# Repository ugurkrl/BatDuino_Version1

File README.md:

BatDuino V1
MAX17040 / MAX17043 + TP4056A + ATMEGA328P

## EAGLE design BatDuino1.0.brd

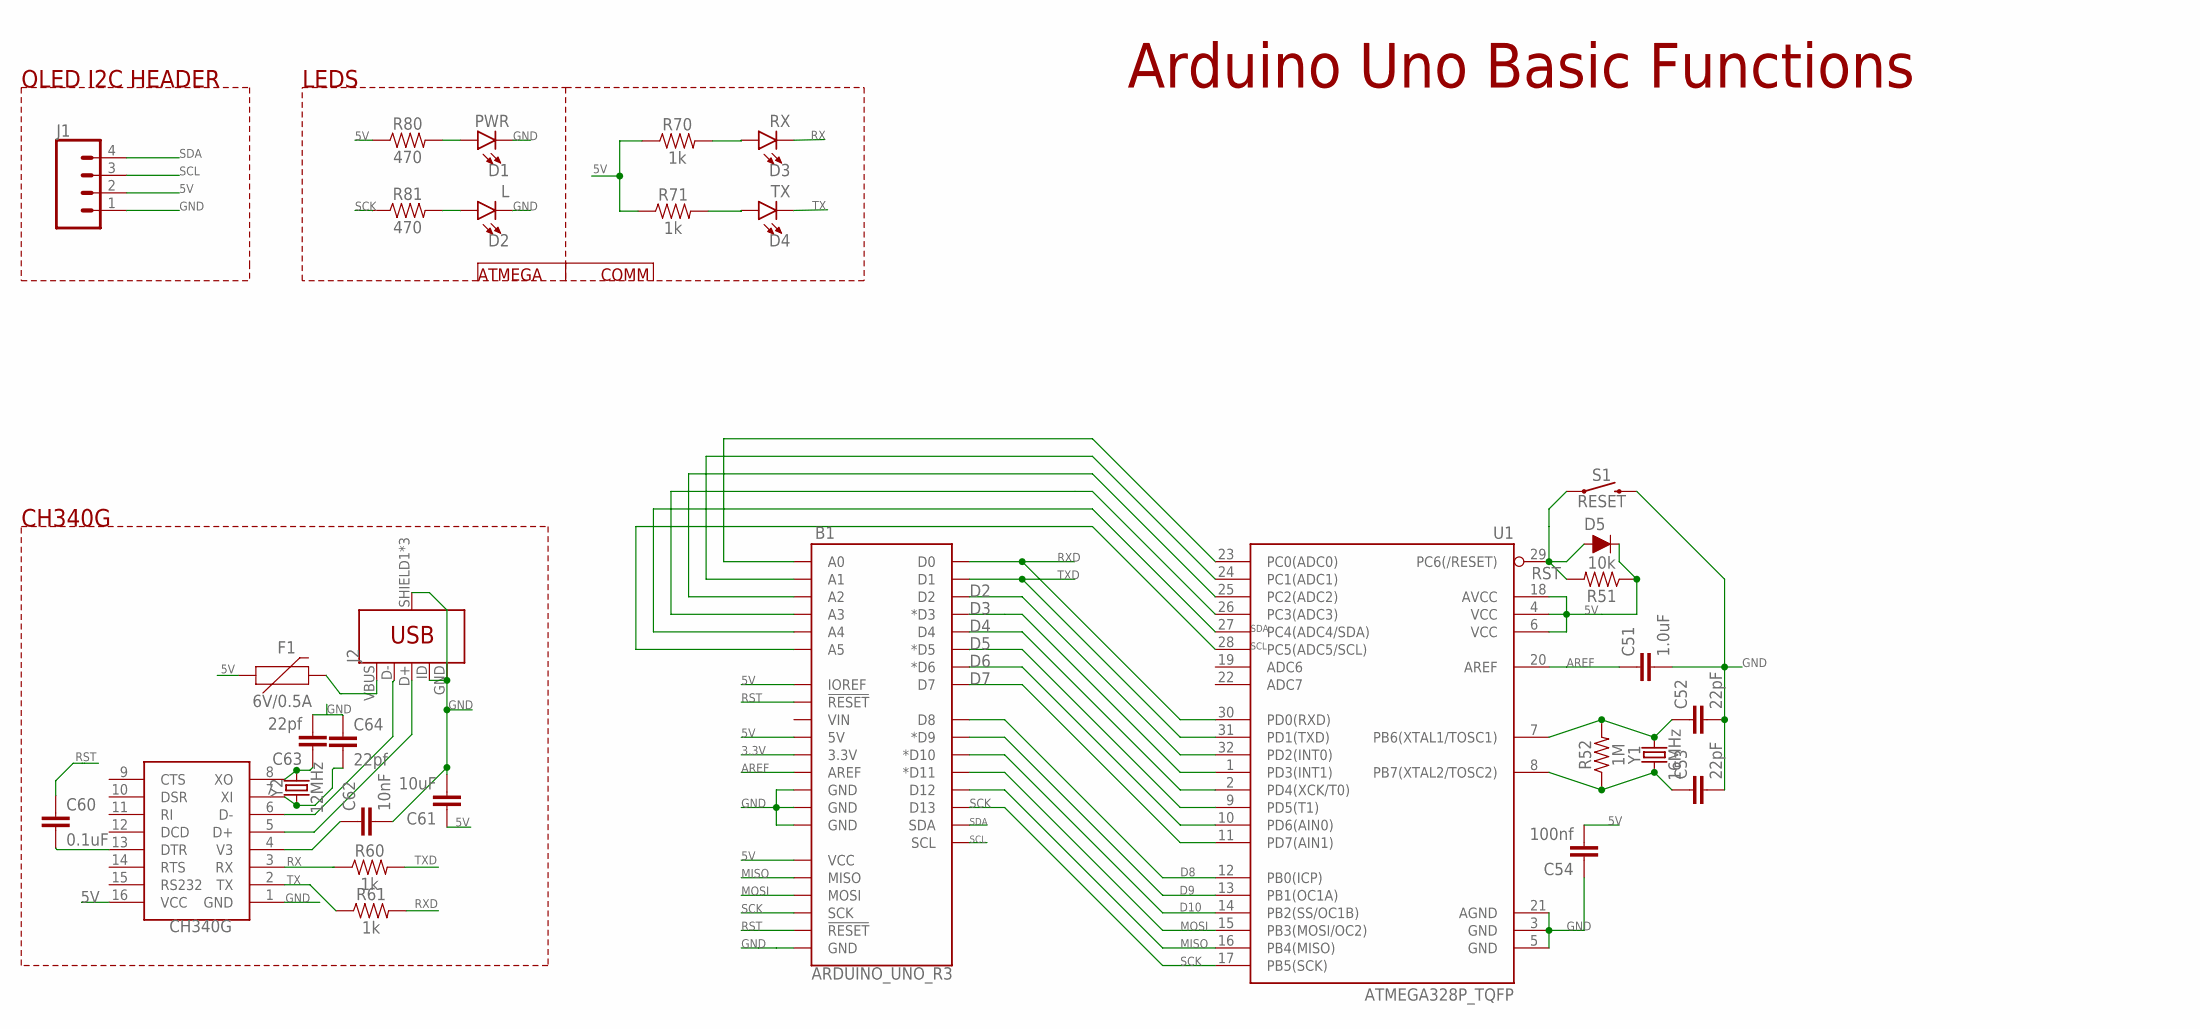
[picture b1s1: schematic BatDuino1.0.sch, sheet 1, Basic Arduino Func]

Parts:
B1: ARDUINO_UNO_R3; ARDUINO_R3
C51: 1.0uF; 0603
C52, C53: 22pF; 0603
C54: 100nf; 0603
C60: 0.1uF; 0603
C61: 10uF; 0603
C62: 10nF; 0603
C63, C64: 22pf; 0603
D1: PWR; LED-0603
D2: L; LED-0603
D3: RX; LED-0603
D4: TX; LED-0603
D5: DIODE-BAS16J; SOD-323
F1: 6V/0.5A; 1206
J1: CONN_04; 1X04
J2: USB_MICRO-BREDUCED_PASTE; USB-B-MICRO-SMD_RED_PASTE
R51: 10k; 0603
R52: 1M; 0603
R60, R61, R70, R71: 1k; 0603
R80, R81: 470; 0603
S1: RESET; TACTILE_SWITCH_PTH_6.0MM
U1: ATMEGA328P_TQFP; TQFP32-08
U$1: CH340G; SOIC16
Y1: 16MHz; HC49US
Y2: 12MHz; HC49US

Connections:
3.3V: B1.3.3V; also elsewhere on the board
5V: B1.5V, B1.IOREF, B1.VCC, C54.2, C61.1, D5.C, F1.1, J1.2, R51.1, R70.1, R71.1, R80.1, U1.4 (VCC), U1.6 (VCC), U1.18 (AVCC), U$1.16 (VCC); also elsewhere on the board
AREF: B1.AREF, C51.1, U1.20 (AREF)
D2: B1.D2, U1.32 (PD2(INT0)); also elsewhere on the board
D3: B1.D3 (*D3), U1.1 (PD3(INT1)); also elsewhere on the board
D4: B1.D4, U1.2 (PD4(XCK/T0)); also elsewhere on the board
D5: B1.D5 (*D5), U1.9 (PD5(T1)); also elsewhere on the board
D6: B1.D6 (*D6), U1.10 (PD6(AIN0)); also elsewhere on the board
D7: B1.D7, U1.11 (PD7(AIN1))
D8: B1.D8, U1.12 (PB0(ICP))
D9: B1.D9 (*D9), U1.13 (PB1(OC1A))
D10: B1.D10 (*D10), U1.14 (PB2(SS/OC1B))
GND: B1.GND@1 (GND), B1.GND@2 (GND), B1.GND@3 (GND), B1.GND@4 (GND), C51.2, C52.2, C53.2, C54.1, C61.2, C62.2, D1.C, D2.C, J1.1, J2.GND, J2.ID, J2.SHIELD1 (SHIELD), J2.SHIELD2 (SHIELD), J2.SHIELD3 (SHIELD), S1.3 (2), U1.3 (GND), U1.5 (GND), U1.21 (AGND), U$1.1 (GND); also elsewhere on the board
MISO: B1.D12, B1.MISO, U1.16 (PB4(MISO))
MOSI: B1.D11 (*D11), B1.MOSI, U1.15 (PB3(MOSI/OC2))
unnamed: C52.1, R52.2, U1.7 (PB6(XTAL1/TOSC1)), Y1.2
unnamed: C53.1, R52.1, U1.8 (PB7(XTAL2/TOSC2)), Y1.1
unnamed: D1.A, R80.2
unnamed: C62.1, U$1.4 (V3)
unnamed: F1.2, J2.VBUS
unnamed: D3.A, R70.2
unnamed: D4.A, R71.2
unnamed: D2.A, R81.2
unnamed: J2.D+, U$1.5 (D+)
unnamed: J2.D-, U$1.6 (D-)
unnamed: B1.A0, U1.23 (PC0(ADC0))
unnamed: B1.A1, U1.24 (PC1(ADC1))
unnamed: B1.A2, U1.25 (PC2(ADC2))
unnamed: B1.A3, U1.26 (PC3(ADC3))
unnamed: C63.1, U$1.8 (XO), Y2.2
unnamed: C64.2, U$1.7 (XI), Y2.1
unnamed: C63.2, C64.1
unnamed: C60.2, U$1.13 (DTR)
RST: B1.RESET@1 (!RESET!), B1.RESET@2 (!RESET!), C60.1, D5.A, R51.2, S1.1, U1.29 (PC6(/RESET))
RX: D3.C, R60.1, U$1.3 (RX)
RXD: B1.D0, R61.2, U1.30 (PD0(RXD))
SCK: B1.D13, B1.SCK, R81.1, U1.17 (PB5(SCK))
SCL: B1.A5, B1.SCL, J1.3, U1.28 (PC5(ADC5/SCL)); also elsewhere on the board
SDA: B1.A4, B1.SDA, J1.4, U1.27 (PC4(ADC4/SDA)); also elsewhere on the board
TX: D4.C, R61.1, U$1.2 (TX)
TXD: B1.D1, R60.2, U1.31 (PD1(TXD))

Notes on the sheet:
Arduino Uno Basic Functions
OLED I2C HEADER
LEDS
ATMEGA
COMM
CH340G

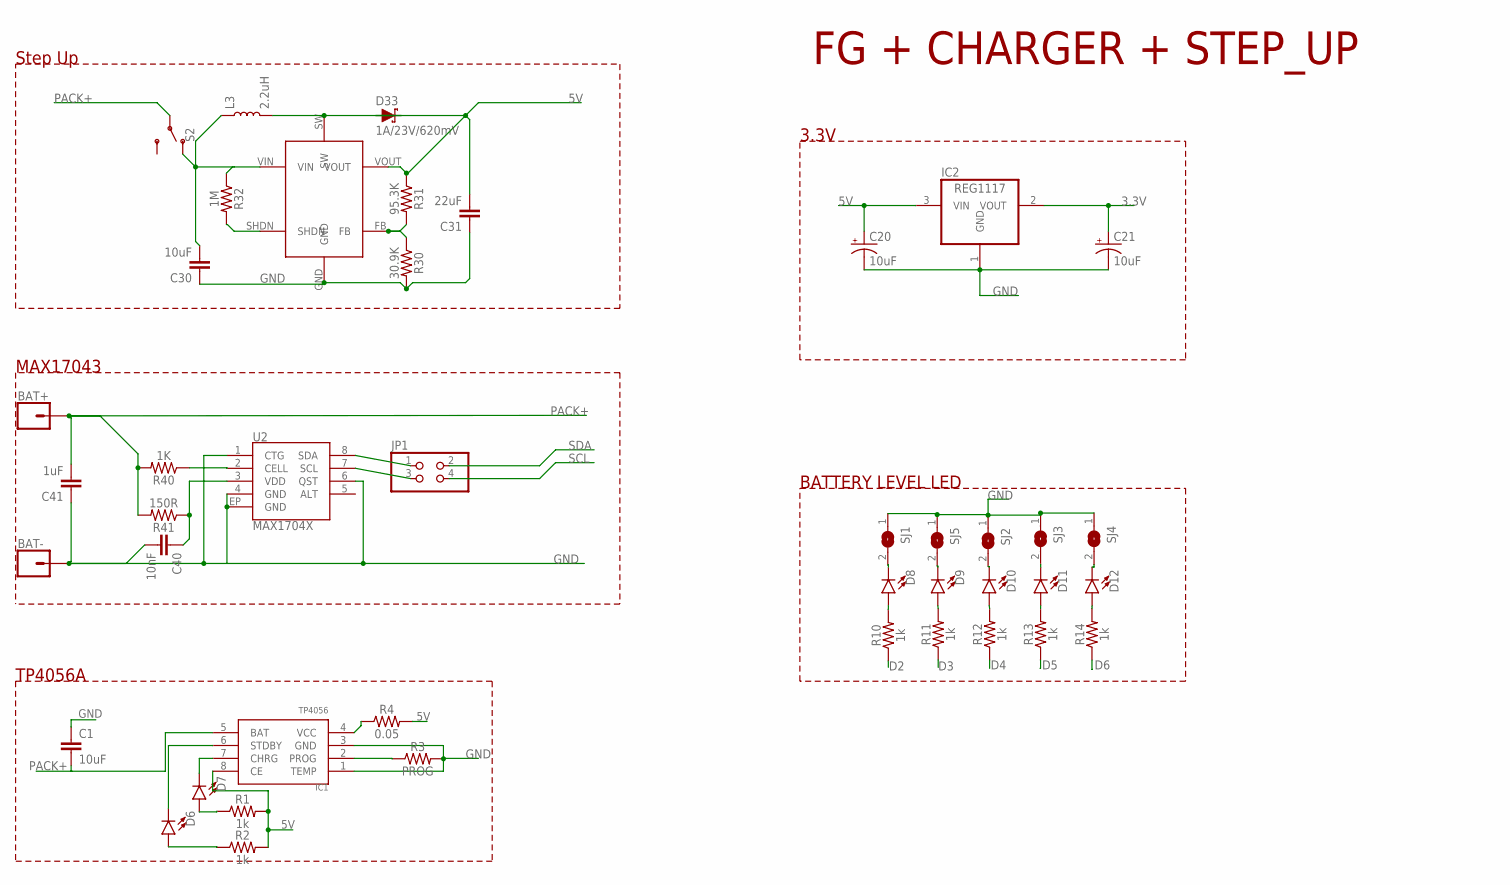
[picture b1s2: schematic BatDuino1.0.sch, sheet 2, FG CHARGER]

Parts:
BAT+: CONN_01; 1X01
BAT-: CONN_01; 1X01
C1, C30: 10uF; 0603
C20, C21: 10uF; EIA3528
C31: 22uF; 0603
C40: 10nF; 0603
C41: 1uF; 0603
D6, D7, D8, D9, D10, D11, D12: LED0603; LED-0603
D33: 1A/23V/620mV; SOD-323
IC1: TP4056; SOP-8
IC2: REG1117; SOT223
JP1: PINHD-2X2; 2X02
L3: 2.2uH; INDUCTOR_4.7UH
R1, R2, R10, R11, R12, R13, R14: 1k; 0603
R3: PROG; AXIAL-0.3
R4: 0.05; 0603
R30: 30.9K; 0603
R31: 95.3K; 0603
R32: 1M; 0603
R40: 1K; 0603
R41: 150R; 0603
S2: SWITCH-SPDT-SMD-RIGHT-ANGLE; SWITCH_SPST_SMD_A
SJ1, SJ2, SJ3, SJ4, SJ5: SJ
U2: MAX1704X; TDFN-8
U$2: XR1151; SOT23-6

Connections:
3.3V: C21.A (+), IC2.2 (VOUT); also elsewhere on the board
5V: C20.A (+), C31.2, D33.A, IC1.8 (CE), IC2.3 (VIN), R1.2, R2.2, R4.2, R31.1, U$2.VOUT; also elsewhere on the board
D2: R10.1; also elsewhere on the board
D3: R11.1; also elsewhere on the board
D4: R12.1; also elsewhere on the board
D5: R13.1; also elsewhere on the board
D6: R14.1; also elsewhere on the board
GND: BAT-.1, C1.1, C20.C (-), C21.C (-), C30.1, C31.1, C40.2, C41.1, IC1.1 (TEMP), IC1.3 (GND), IC2.1 (GND), R3.P$2 (2), R30.2, SJ1.1, SJ2.1, SJ3.1, SJ4.1, SJ5.1, U2.1 (CTG), U2.4 (GND), U2.6 (QST), U2.EP (GND), U$2.GND; also elsewhere on the board
unnamed: R40.1, U2.2 (CELL)
unnamed: C40.1, R41.1, U2.3 (VDD)
unnamed: JP1.1, U2.8 (SDA)
unnamed: D6.C, IC1.6 (STDBY)
unnamed: JP1.3, U2.7 (SCL)
unnamed: D7.C, IC1.7 (CHRG)
unnamed: D7.A, R1.1
unnamed: D6.A, R2.1
unnamed: IC1.4 (VCC), R4.1
unnamed: IC1.2 (PROG), R3.P$1 (1)
unnamed: C30.2, L3.P$1 (1), R32.1, S2.1 (O), U$2.VIN
unnamed: D8.C, SJ1.2
unnamed: D9.C, SJ5.2
unnamed: D10.C, SJ2.2
unnamed: D11.C, SJ3.2
unnamed: D12.C, SJ4.2
unnamed: D33.C, L3.P$2 (2), U$2.SW
unnamed: D8.A, R10.2
unnamed: D9.A, R11.2
unnamed: D10.A, R12.2
unnamed: D11.A, R13.2
unnamed: D12.A, R14.2
unnamed: R30.1, R31.2, U$2.FB
unnamed: R32.2, U$2.SHDN
PACK+: BAT+.1, C1.2, C41.2, IC1.5 (BAT), R40.2, R41.2, S2.2
SCL: JP1.4; also elsewhere on the board
SDA: JP1.2; also elsewhere on the board

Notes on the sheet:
FG + CHARGER + STEP_UP
Step Up
3.3V
TP4056A
MAX17043
BATTERY LEVEL LED

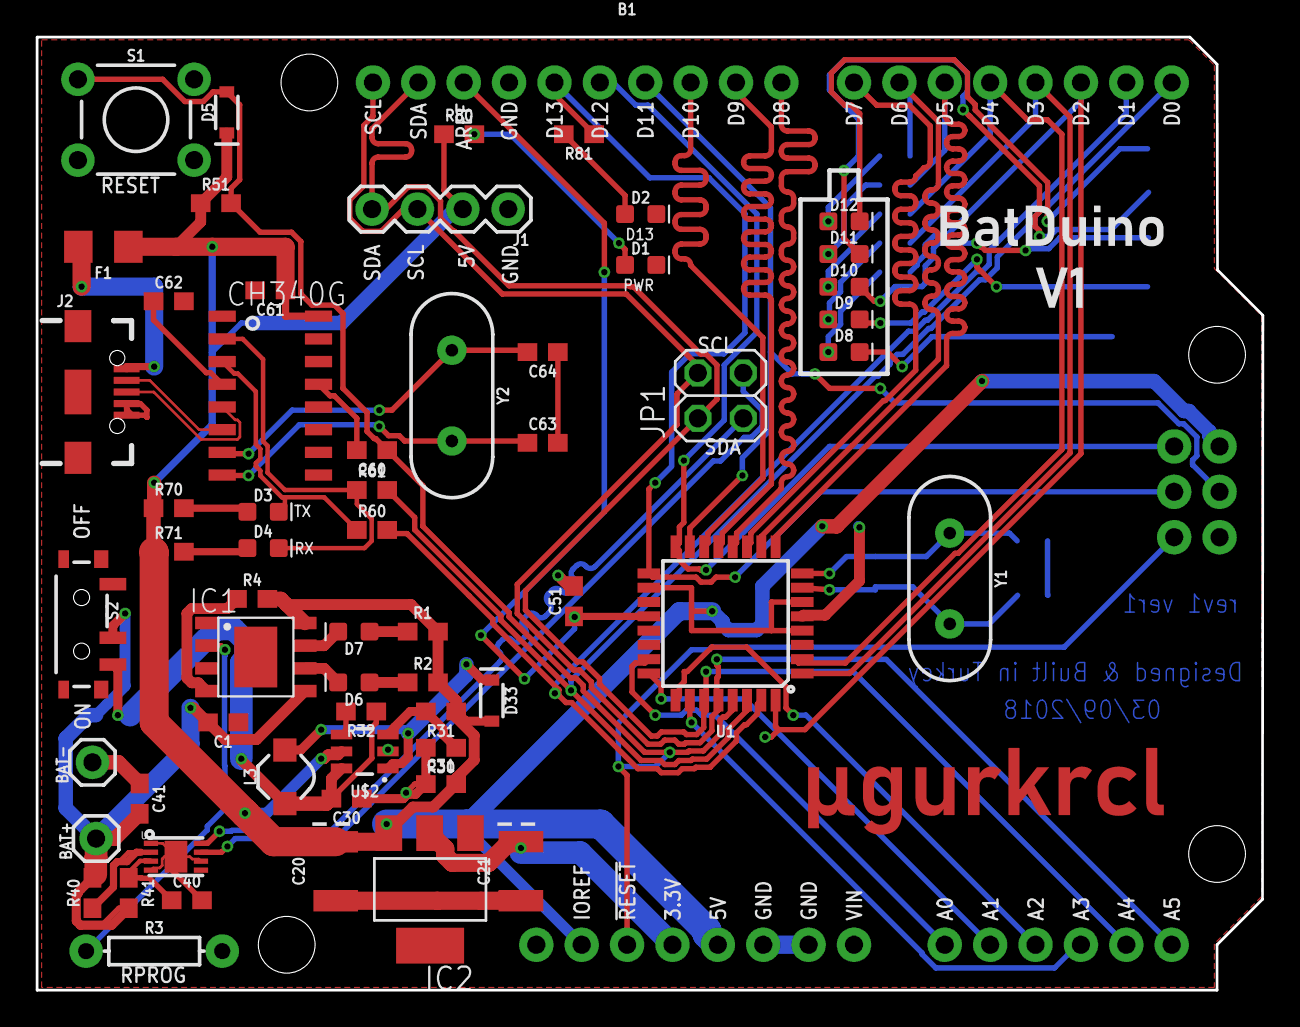
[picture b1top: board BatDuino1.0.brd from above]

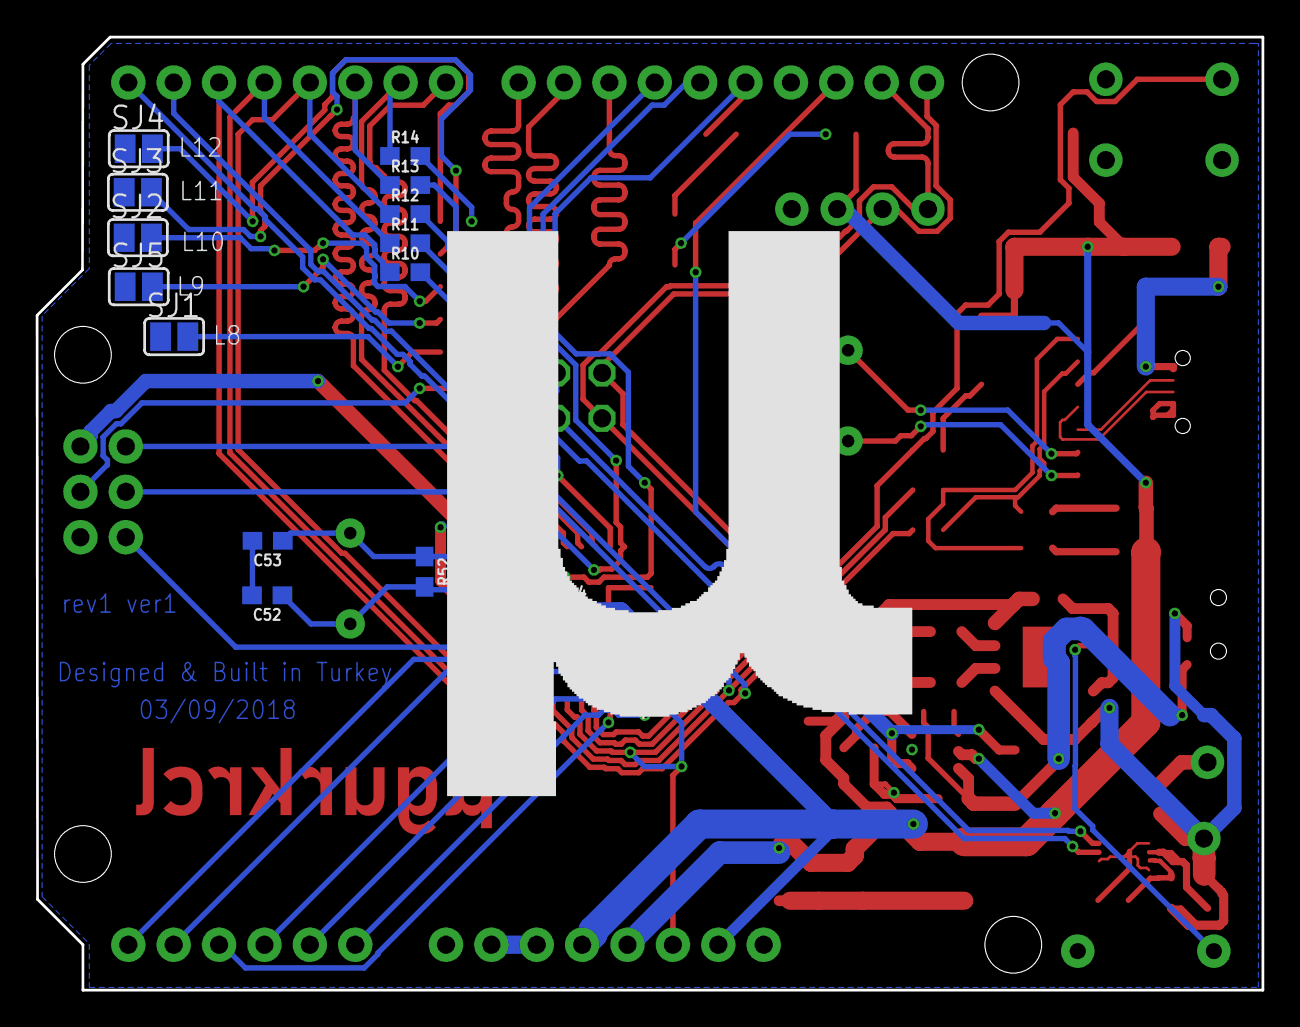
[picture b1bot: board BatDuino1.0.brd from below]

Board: 2 copper layers, 68.6 x 53.3 mm, 74 parts (14 on the bottom side), 66 nets.

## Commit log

2018-12-07 Ver1 Rev1 first commit
2019-08-07 add demo sketch

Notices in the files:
parts and their libraries:
SparkFun-IC-Microcontroller: Licensing: Creative Commons ShareAlike 4.0 International - https://creativecommons.org/licenses/by-sa/4.0
